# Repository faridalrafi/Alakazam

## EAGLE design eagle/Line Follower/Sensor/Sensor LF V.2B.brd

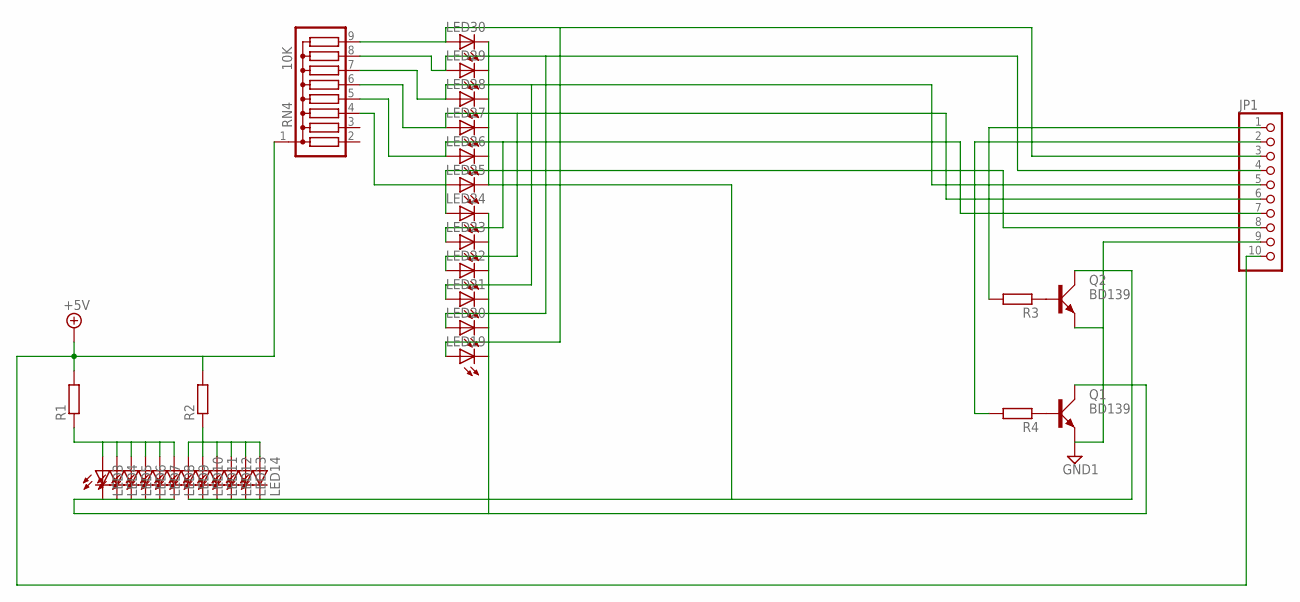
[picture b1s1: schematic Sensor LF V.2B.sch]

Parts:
JP1: PINHD-1X10; 1X10
LED3, LED4, LED5, LED6, LED7, LED8, LED9, LED10, LED11, LED12, LED13, LED14, LED19, LED20, LED21, LED22, LED23, LED24, LED25, LED26, LED27, LED28, LED29, LED30: LED3MM
Q1, Q2: BD139; TO126AV
R1, R2, R3, R4: R-EU_0207/10; 0207/10
RN4: 10K; SIL9

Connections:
+5V: JP1.10, R1.2, R2.2, RN4.1
GND1: JP1.9, Q1.E, Q2.E
unnamed: LED9.K (C), LED10.K (C), LED11.K (C), LED12.K (C), LED13.K (C), LED14.K (C), LED25.K (C), LED26.K (C), LED27.K (C), LED28.K (C), LED29.K (C), LED30.K (C), Q2.C
unnamed: LED3.K (C), LED4.K (C), LED5.K (C), LED6.K (C), LED7.K (C), LED8.K (C), LED19.K (C), LED20.K (C), LED21.K (C), LED22.K (C), LED23.K (C), LED24.K (C), Q1.C
unnamed: Q2.B, R3.1
unnamed: Q1.B, R4.1
unnamed: JP1.1, R3.2
unnamed: JP1.2, R4.2
unnamed: JP1.8, LED24.A, LED25.A, RN4.4
unnamed: JP1.7, LED23.A, LED26.A, RN4.5
unnamed: JP1.6, LED22.A, LED27.A, RN4.6
unnamed: JP1.5, LED21.A, LED28.A, RN4.7
unnamed: JP1.4, LED20.A, LED29.A, RN4.8
unnamed: JP1.3, LED19.A, LED30.A, RN4.9
unnamed: LED3.A, LED4.A, LED5.A, LED6.A, LED7.A, LED8.A, R1.1
unnamed: LED9.A, LED10.A, LED11.A, LED12.A, LED13.A, LED14.A, R2.1

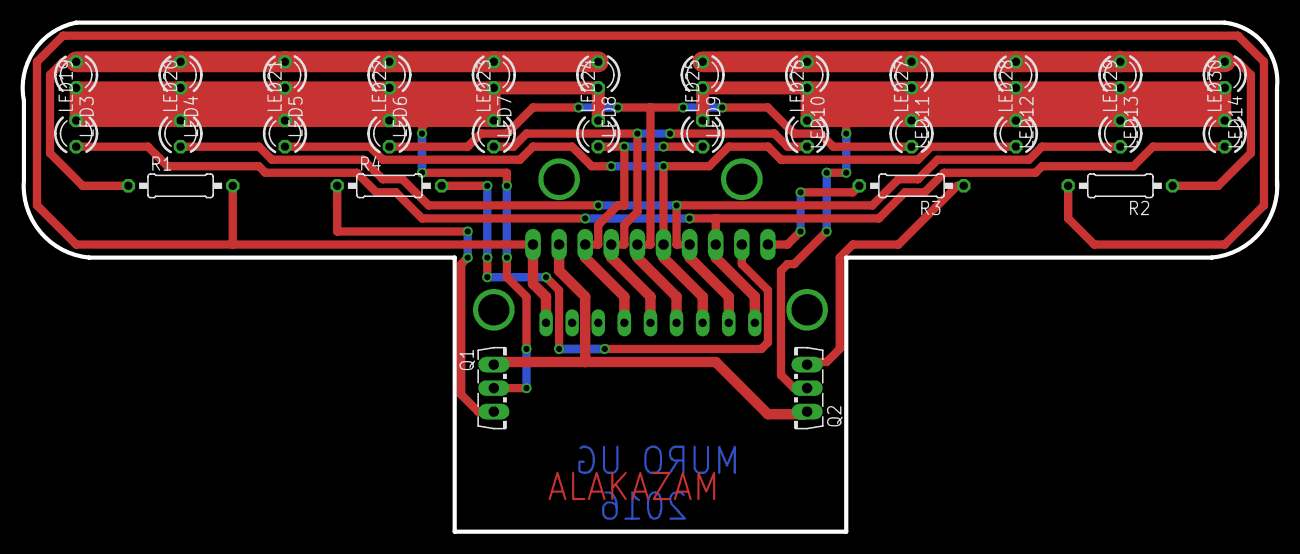
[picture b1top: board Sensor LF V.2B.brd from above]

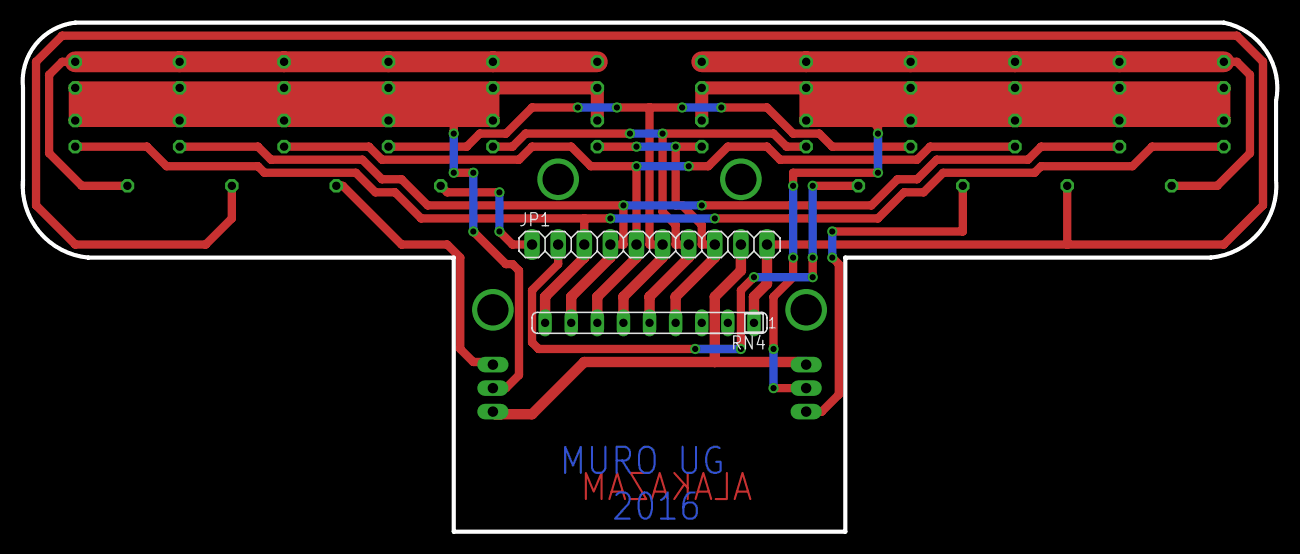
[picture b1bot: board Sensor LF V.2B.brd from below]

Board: 2 copper layers, 122.1 x 49.5 mm, 32 parts (2 on the bottom side), 16 nets.

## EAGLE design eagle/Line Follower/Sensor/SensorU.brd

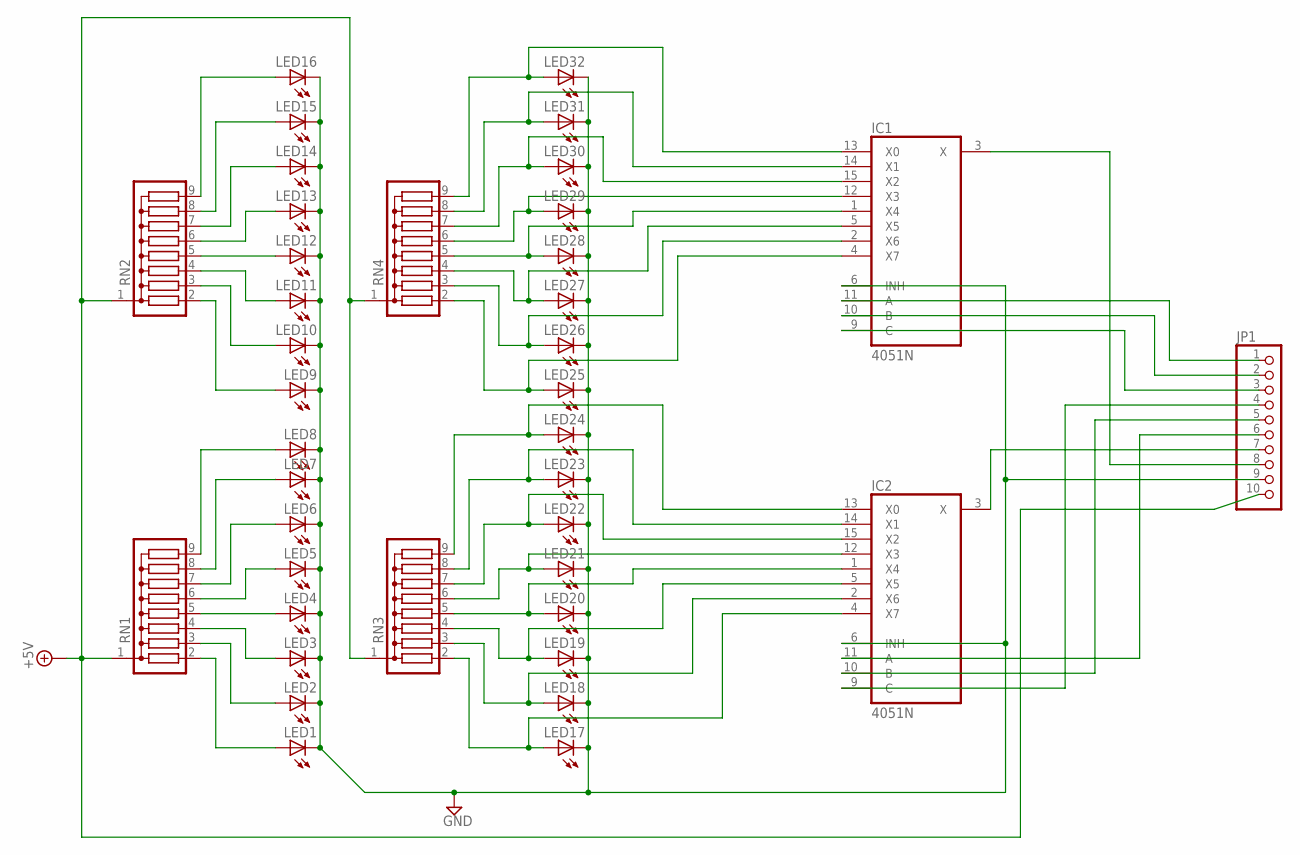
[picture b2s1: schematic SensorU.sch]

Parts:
IC1, IC2: 4051N; DIL16
JP1: PINHD-1X10; 1X10
LED1, LED2, LED3, LED4, LED5, LED6, LED7, LED8, LED9, LED10, LED11, LED12, LED13, LED14, LED15, LED16, LED17, LED18, LED19, LED20, LED21, LED22, LED23, LED24, LED25, LED26, LED27, LED28, LED29, LED30, LED31, LED32: LED3MM
RN1, RN2, RN3, RN4: G08R; SIL9

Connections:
+5V: IC1.16 (VCC), IC2.16 (VCC), JP1.10, RN1.1, RN2.1, RN3.1, RN4.1
GND: IC1.6 (INH), IC1.7 (VEE), IC1.8 (GND), IC2.6 (INH), IC2.7 (VEE), IC2.8 (GND), JP1.9, LED1.K (C), LED2.K (C), LED3.K (C), LED4.K (C), LED5.K (C), LED6.K (C), LED7.K (C), LED8.K (C), LED9.K (C), LED10.K (C), LED11.K (C), LED12.K (C), LED13.K (C), LED14.K (C), LED15.K (C), LED16.K (C), LED17.K (C), LED18.K (C), LED19.K (C), LED20.K (C), LED21.K (C), LED22.K (C), LED23.K (C), LED24.K (C), LED25.K (C), LED26.K (C), LED27.K (C), LED28.K (C), LED29.K (C), LED30.K (C), LED31.K (C), LED32.K (C)
unnamed: LED16.A, RN2.9
unnamed: LED15.A, RN2.8
unnamed: LED14.A, RN2.7
unnamed: LED13.A, RN2.6
unnamed: LED12.A, RN2.5
unnamed: LED11.A, RN2.4
unnamed: LED10.A, RN2.3
unnamed: LED9.A, RN2.2
unnamed: LED1.A, RN1.2
unnamed: LED2.A, RN1.3
unnamed: LED3.A, RN1.4
unnamed: LED4.A, RN1.5
unnamed: LED5.A, RN1.6
unnamed: LED6.A, RN1.7
unnamed: LED7.A, RN1.8
unnamed: LED8.A, RN1.9
unnamed: IC2.3 (X), JP1.7
unnamed: IC1.3 (X), JP1.8
unnamed: IC1.11 (A), JP1.1
unnamed: IC1.10 (B), JP1.2
unnamed: IC1.9 (C), JP1.3
unnamed: IC2.9 (C), JP1.4
unnamed: IC2.10 (B), JP1.5
unnamed: IC2.11 (A), JP1.6
unnamed: IC1.13 (X0), LED32.A, RN4.9
unnamed: IC1.14 (X1), LED31.A, RN4.8
unnamed: IC1.15 (X2), LED30.A, RN4.7
unnamed: IC1.12 (X3), LED29.A, RN4.6
unnamed: IC1.1 (X4), LED28.A, RN4.5
unnamed: IC1.5 (X5), LED27.A, RN4.4
unnamed: IC1.2 (X6), LED26.A, RN4.3
unnamed: IC1.4 (X7), LED25.A, RN4.2
unnamed: IC2.13 (X0), LED24.A, RN3.9
unnamed: IC2.14 (X1), LED23.A, RN3.8
unnamed: IC2.15 (X2), LED22.A, RN3.7
unnamed: IC2.12 (X3), LED21.A, RN3.6
unnamed: IC2.1 (X4), LED20.A, RN3.5
unnamed: IC2.5 (X5), LED19.A, RN3.4
unnamed: IC2.2 (X6), LED18.A, RN3.3
unnamed: IC2.4 (X7), LED17.A, RN3.2

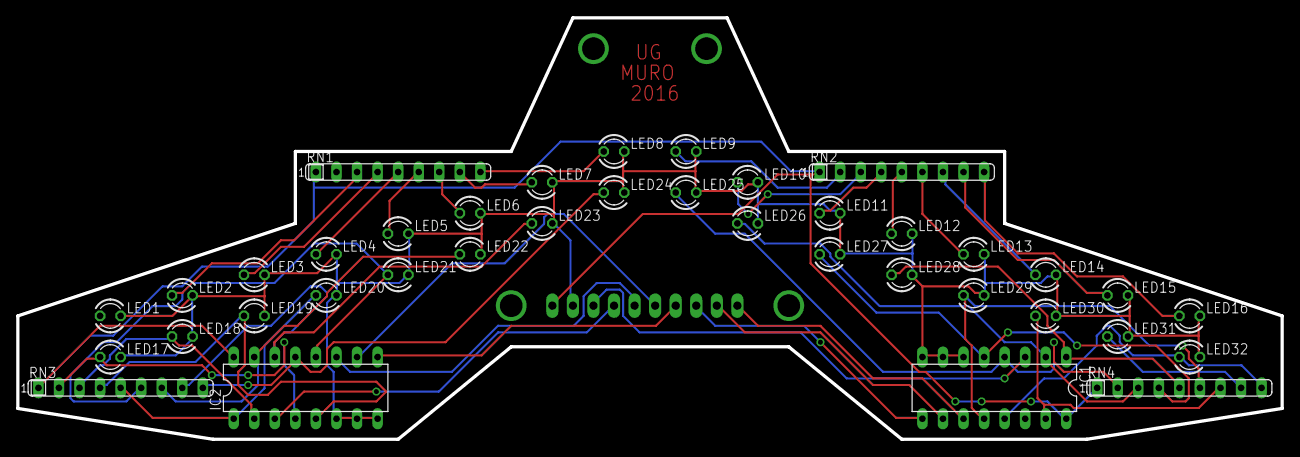
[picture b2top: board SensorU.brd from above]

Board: 2 copper layers, 156.2 x 52.1 mm, 39 parts (1 on the bottom side), 42 nets.

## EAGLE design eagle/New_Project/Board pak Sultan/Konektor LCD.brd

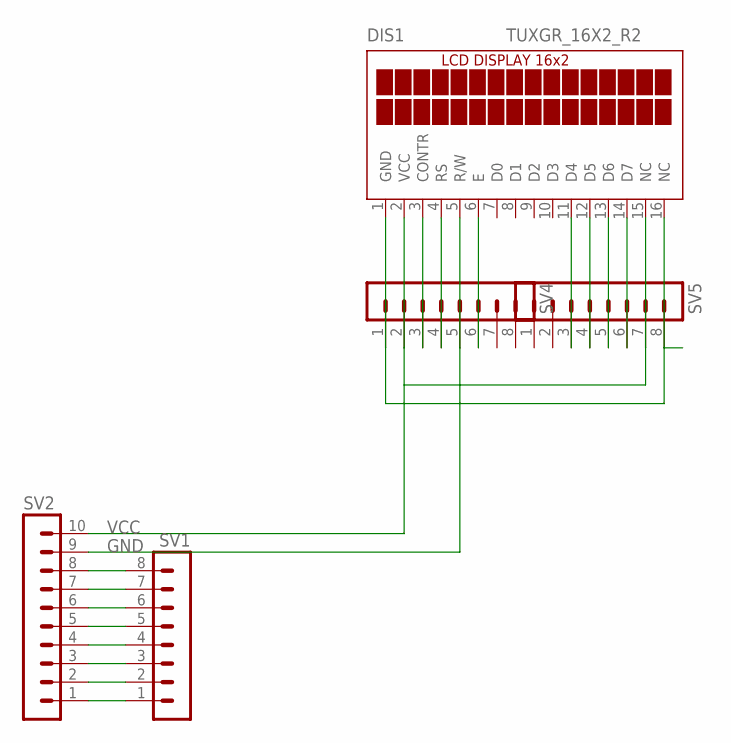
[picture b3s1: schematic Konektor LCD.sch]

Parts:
DIS1: TUXGR_16X2_R2
SV1, SV4, SV5: MA08-1
SV2: MA10-1

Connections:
GND: DIS1.1 (GND), DIS1.5 (R/W), DIS1.16 (NC), SV2.9, SV4.1, SV4.5, SV5.8
unnamed: SV1.1, SV2.1
unnamed: SV1.2, SV2.2
unnamed: SV1.3, SV2.3
unnamed: SV1.4, SV2.4
unnamed: SV1.5, SV2.5
unnamed: SV1.6, SV2.6
unnamed: SV1.7, SV2.7
unnamed: SV1.8, SV2.8
unnamed: DIS1.3 (CONTR), SV4.3
unnamed: DIS1.4 (RS), SV4.4
unnamed: DIS1.6 (E), SV4.6
unnamed: DIS1.14 (D7), SV5.6
unnamed: DIS1.13 (D6), SV5.5
unnamed: DIS1.12 (D5), SV5.4
unnamed: DIS1.11 (D4), SV5.3
VCC: DIS1.2 (VCC), DIS1.15 (NC), SV2.10, SV4.2, SV5.7

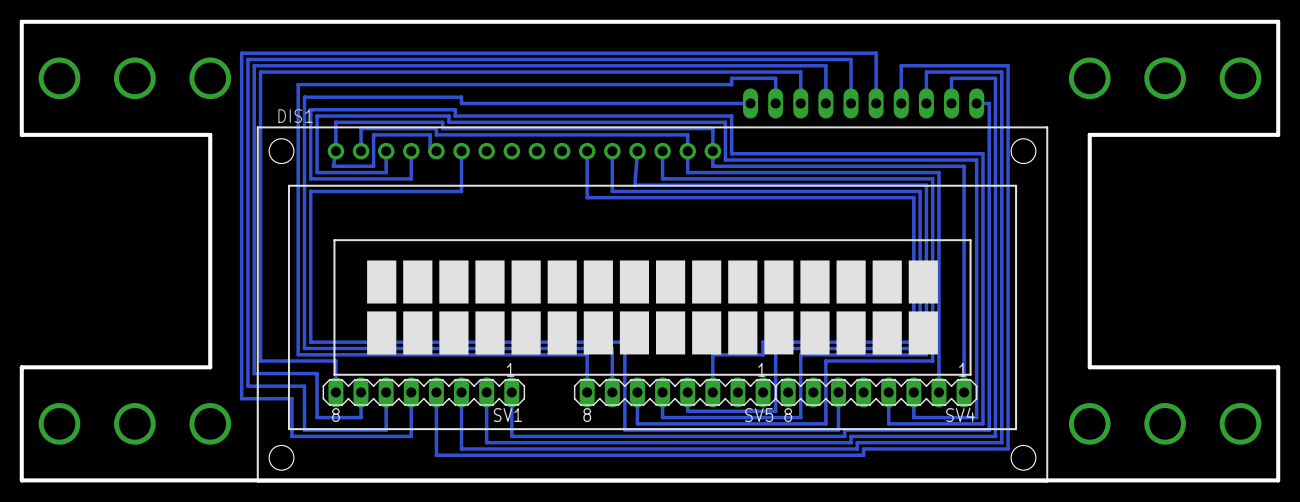
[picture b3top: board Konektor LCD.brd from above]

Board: 2 copper layers, 127.0 x 46.4 mm, 5 parts (1 on the bottom side), 17 nets.
